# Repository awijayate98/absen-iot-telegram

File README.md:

# absen-iot-telegram

Sistem Absen Menggunaka esp32 + rfid dan di integrasikan dengan database ,dan notifikasi via telegram apabila ada data member baru dan juga ketika tap absen ,dan juga menggunakan tampilan web

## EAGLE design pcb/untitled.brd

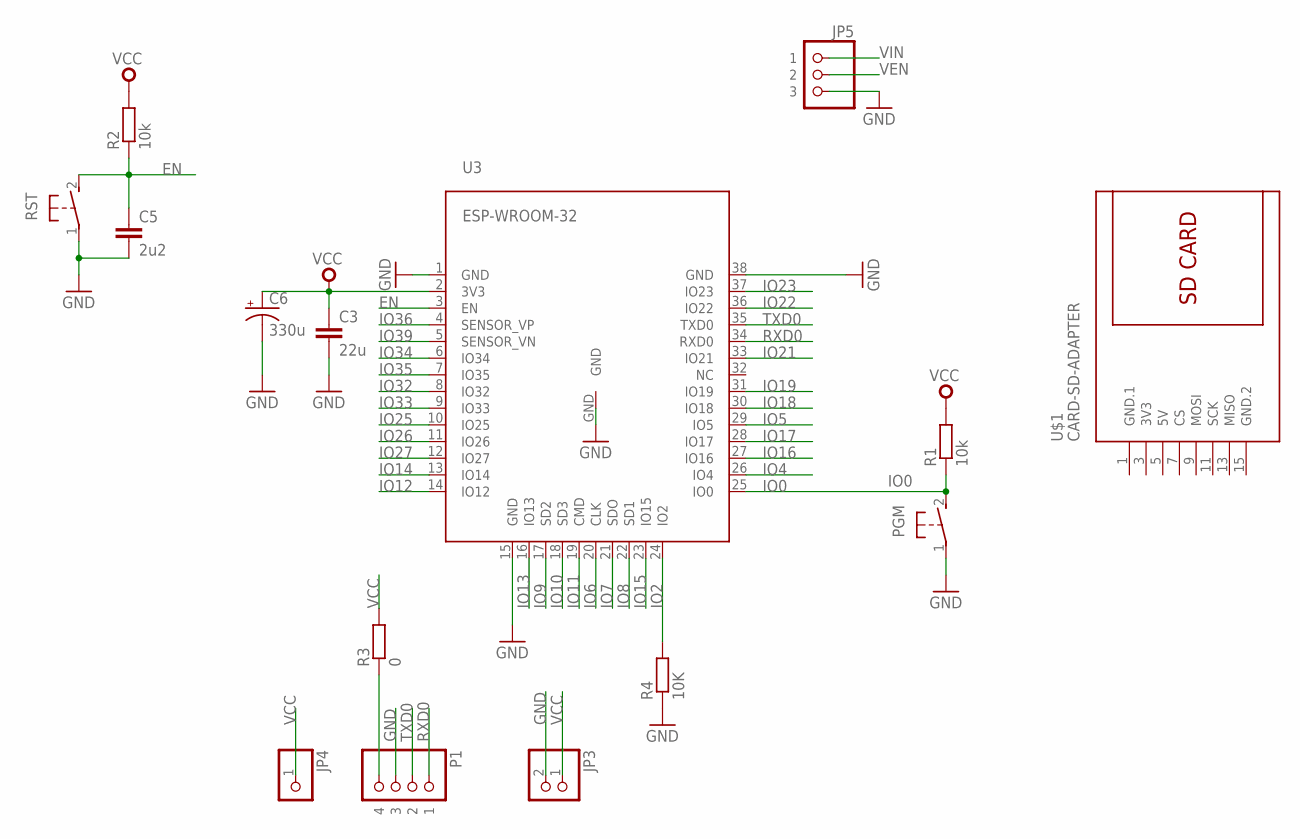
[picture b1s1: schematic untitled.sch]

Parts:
C3: 22u; 0805
C5: 2u2; C0603
C6: 330u; VISHAY_C
JP3: HEADER-1X2ROUND; 1X02_ROUND
JP4: HEADER-1X1ROUND; 1X01_ROUND
JP5: HEADER-1X3ROUND; 1X03_ROUND
P1: HEADER-1X4ROUND; 1X04_ROUND
PGM: DTSM-3
R1, R2: 10k; R0603
R3: 0; R0603
R4: 10K; R0603
RST: DTSM-3
U3: ESP-WROOM-32
U$1: CARD-SD-ADAPTER

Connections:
3V3: U$1.3 (3V3)
5V: U$1.5 (5V)
EN: C5.1, R2.1, RST.2, U3.3 (EN)
GND: C3.2, C5.2, C6.-, JP3.2, JP5.3, P1.3, PGM.1, R4.1, RST.1, U3.1 (GND), U3.15 (GND), U3.38 (GND), U3.GND
GND.1: U$1.1 (GND.1)
GND.2: U$1.15 (GND.2)
IO0: PGM.2, R1.1, U3.25 (IO0)
IO2: R4.2, U3.24 (IO2)
IO4: U3.26 (IO4)
IO5: U3.29 (IO5)
IO6: U3.20 (CLK)
IO7: U3.21 (SDO)
IO8: U3.22 (SD1)
IO9: U3.17 (SD2)
IO10: U3.18 (SD3)
IO11: U3.19 (CMD)
IO12: U3.14 (IO12)
IO13: U3.16 (IO13)
IO14: U3.13 (IO14)
IO15: U3.23 (IO15)
IO16: U3.27 (IO16)
IO17: U3.28 (IO17)
IO18: U3.30 (IO18)
IO19: U3.31 (IO19)
IO21: U3.33 (IO21)
IO22: U3.36 (IO22)
IO23: U3.37 (IO23)
IO25: U3.10 (IO25)
IO26: U3.11 (IO26)
IO27: U3.12 (IO27)
IO32: U3.8 (IO32)
IO33: U3.9 (IO33)
IO34: U3.6 (IO34)
IO35: U3.7 (IO35)
IO36: U3.4 (SENSOR_VP)
IO39: U3.5 (SENSOR_VN)
unnamed: P1.4, R3.1
RXD0: P1.1, U3.34 (RXD0)
TXD0: P1.2, U3.35 (TXD0)
VCC: C3.1, C6.+, JP3.1, JP4.1, R1.2, R2.2, R3.2, U3.2 (3V3)
VEN: JP5.2
VIN: JP5.1

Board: 2 copper layers, 15 parts (10 on the bottom side), 8 nets, no tracks yet.

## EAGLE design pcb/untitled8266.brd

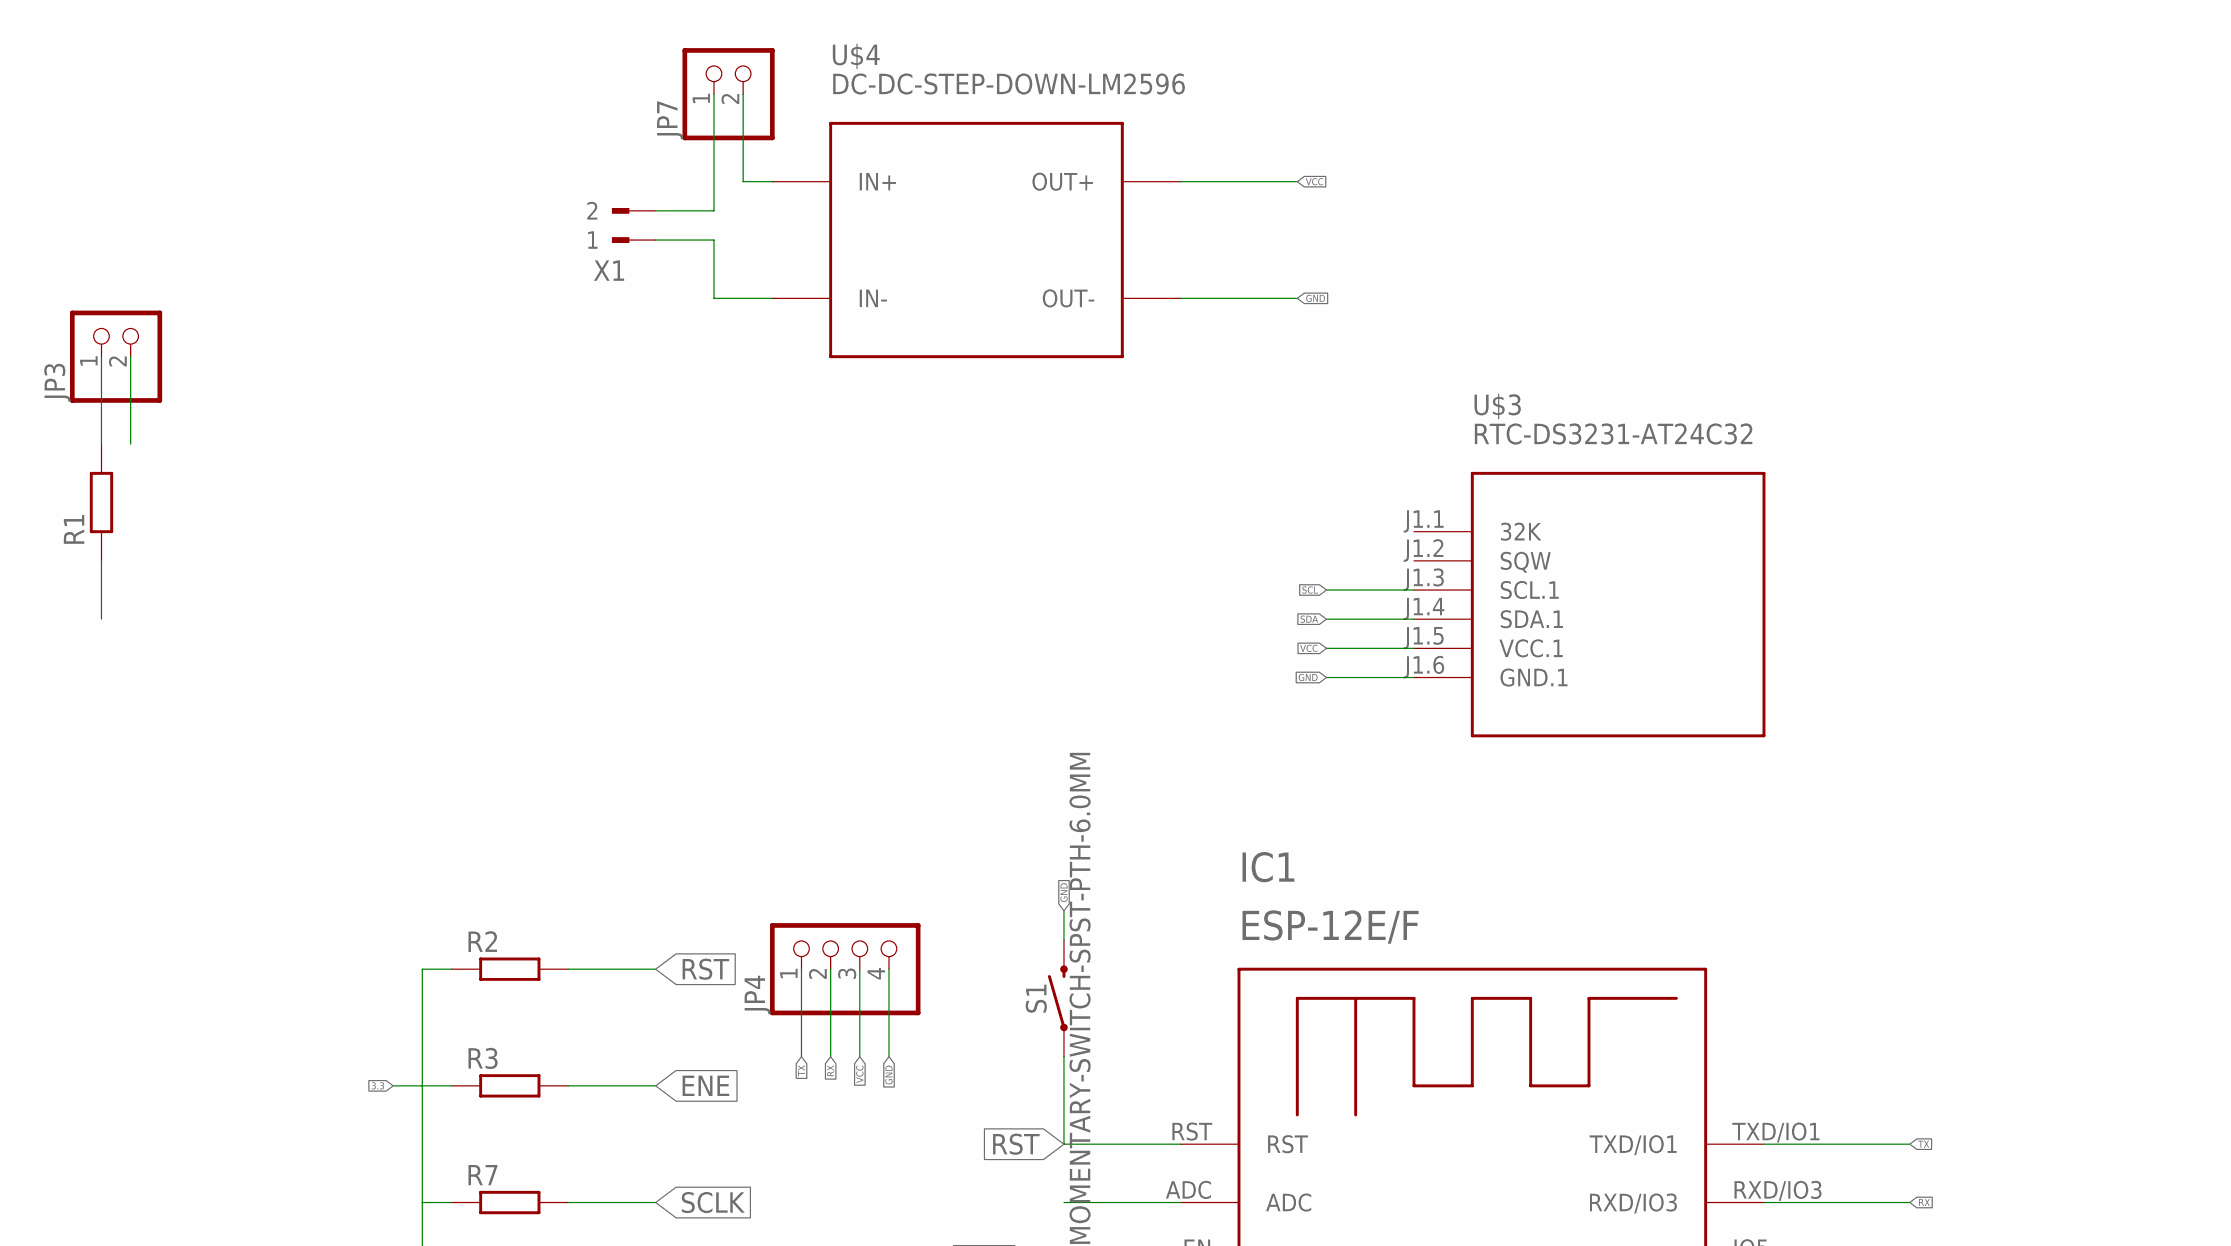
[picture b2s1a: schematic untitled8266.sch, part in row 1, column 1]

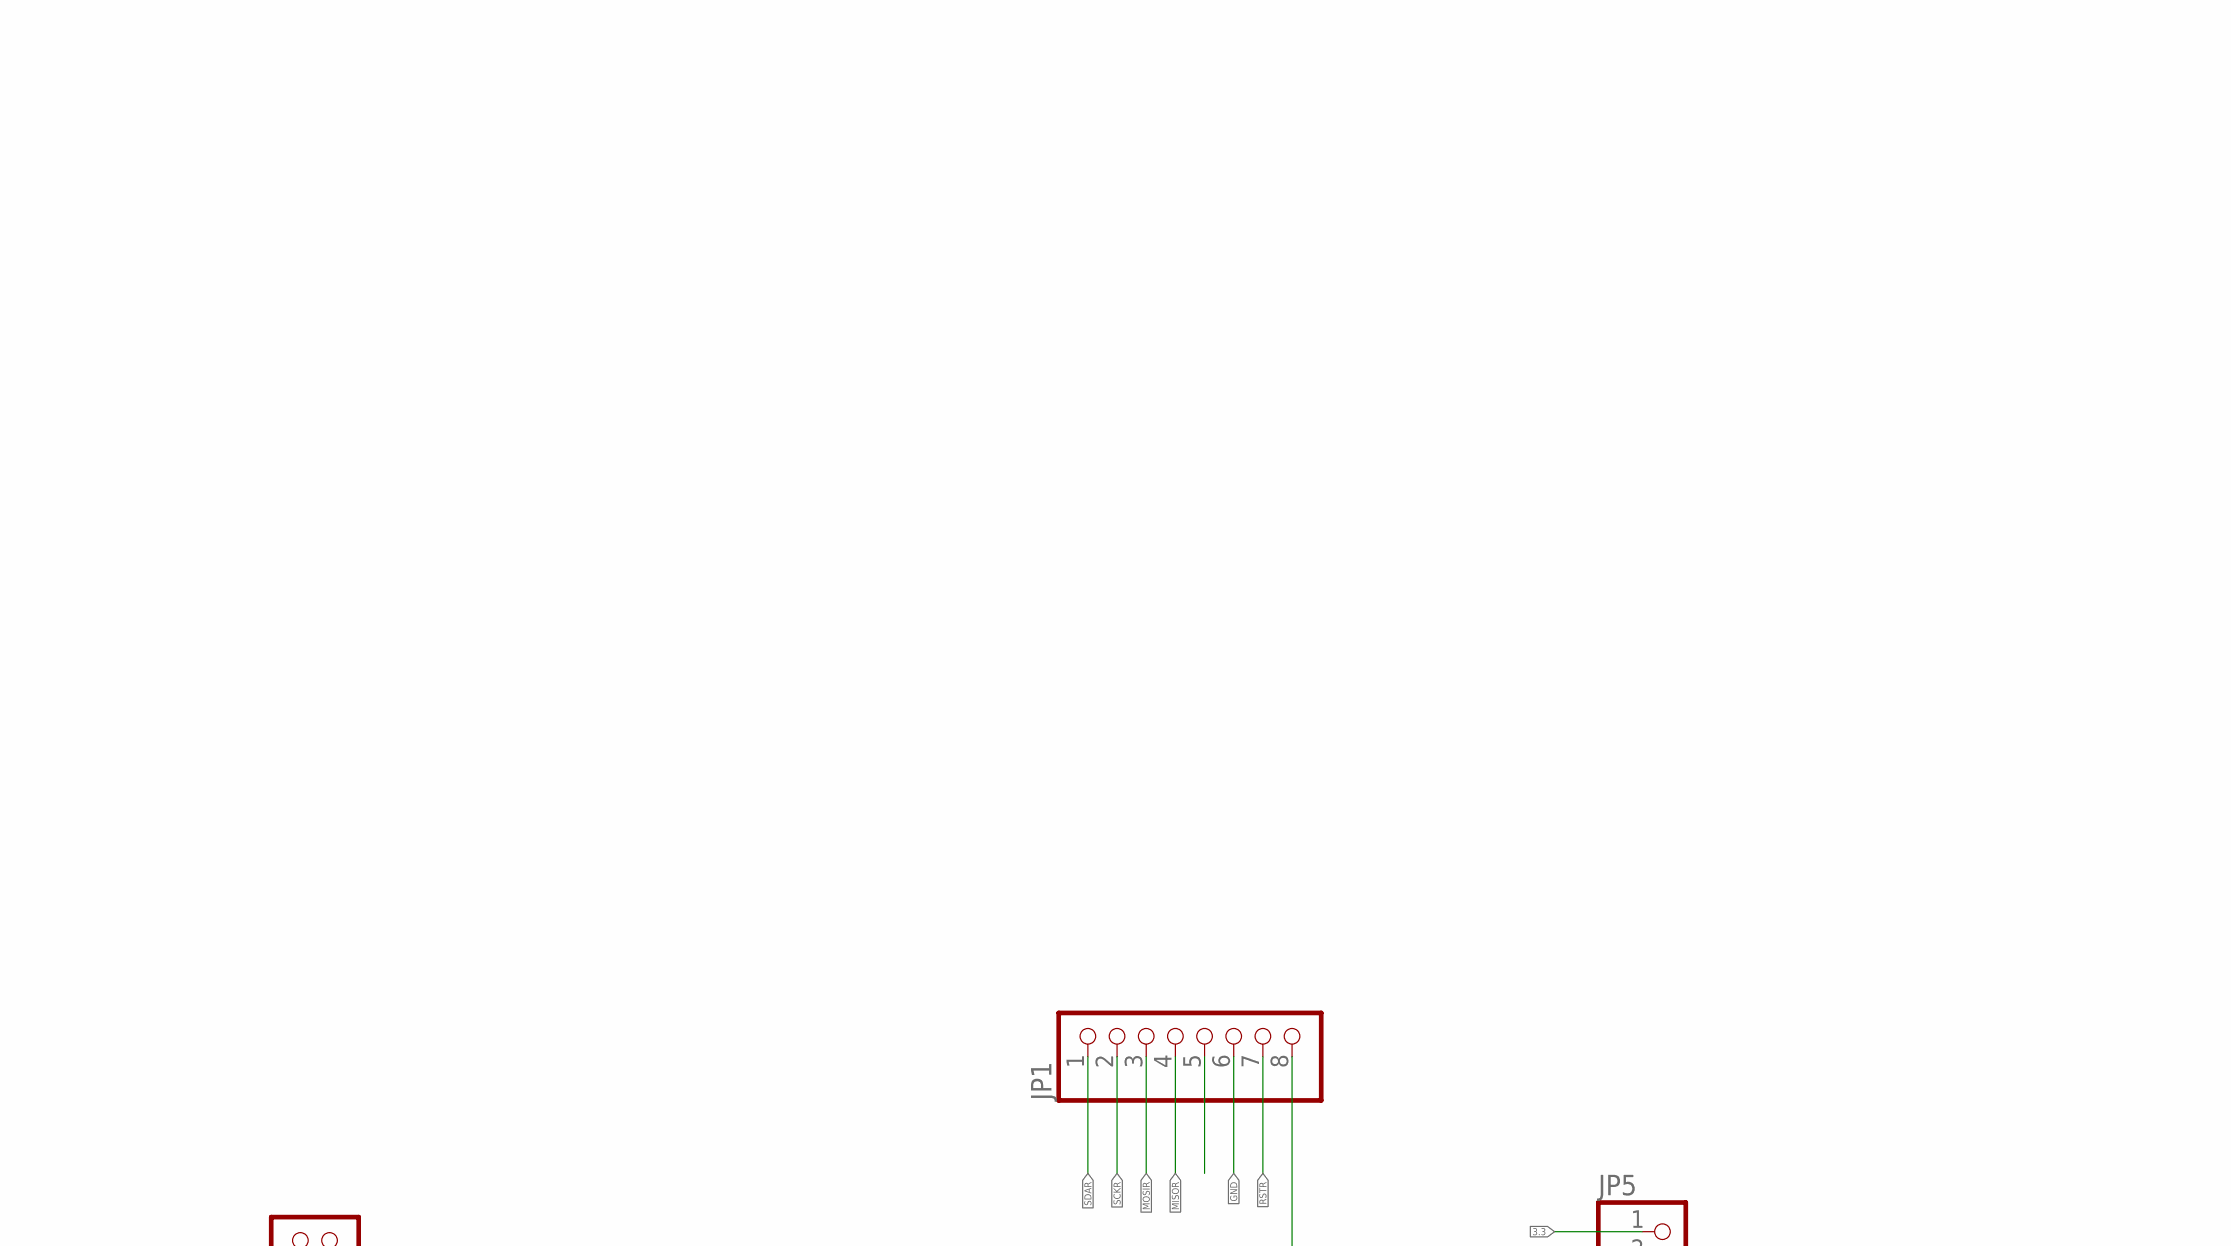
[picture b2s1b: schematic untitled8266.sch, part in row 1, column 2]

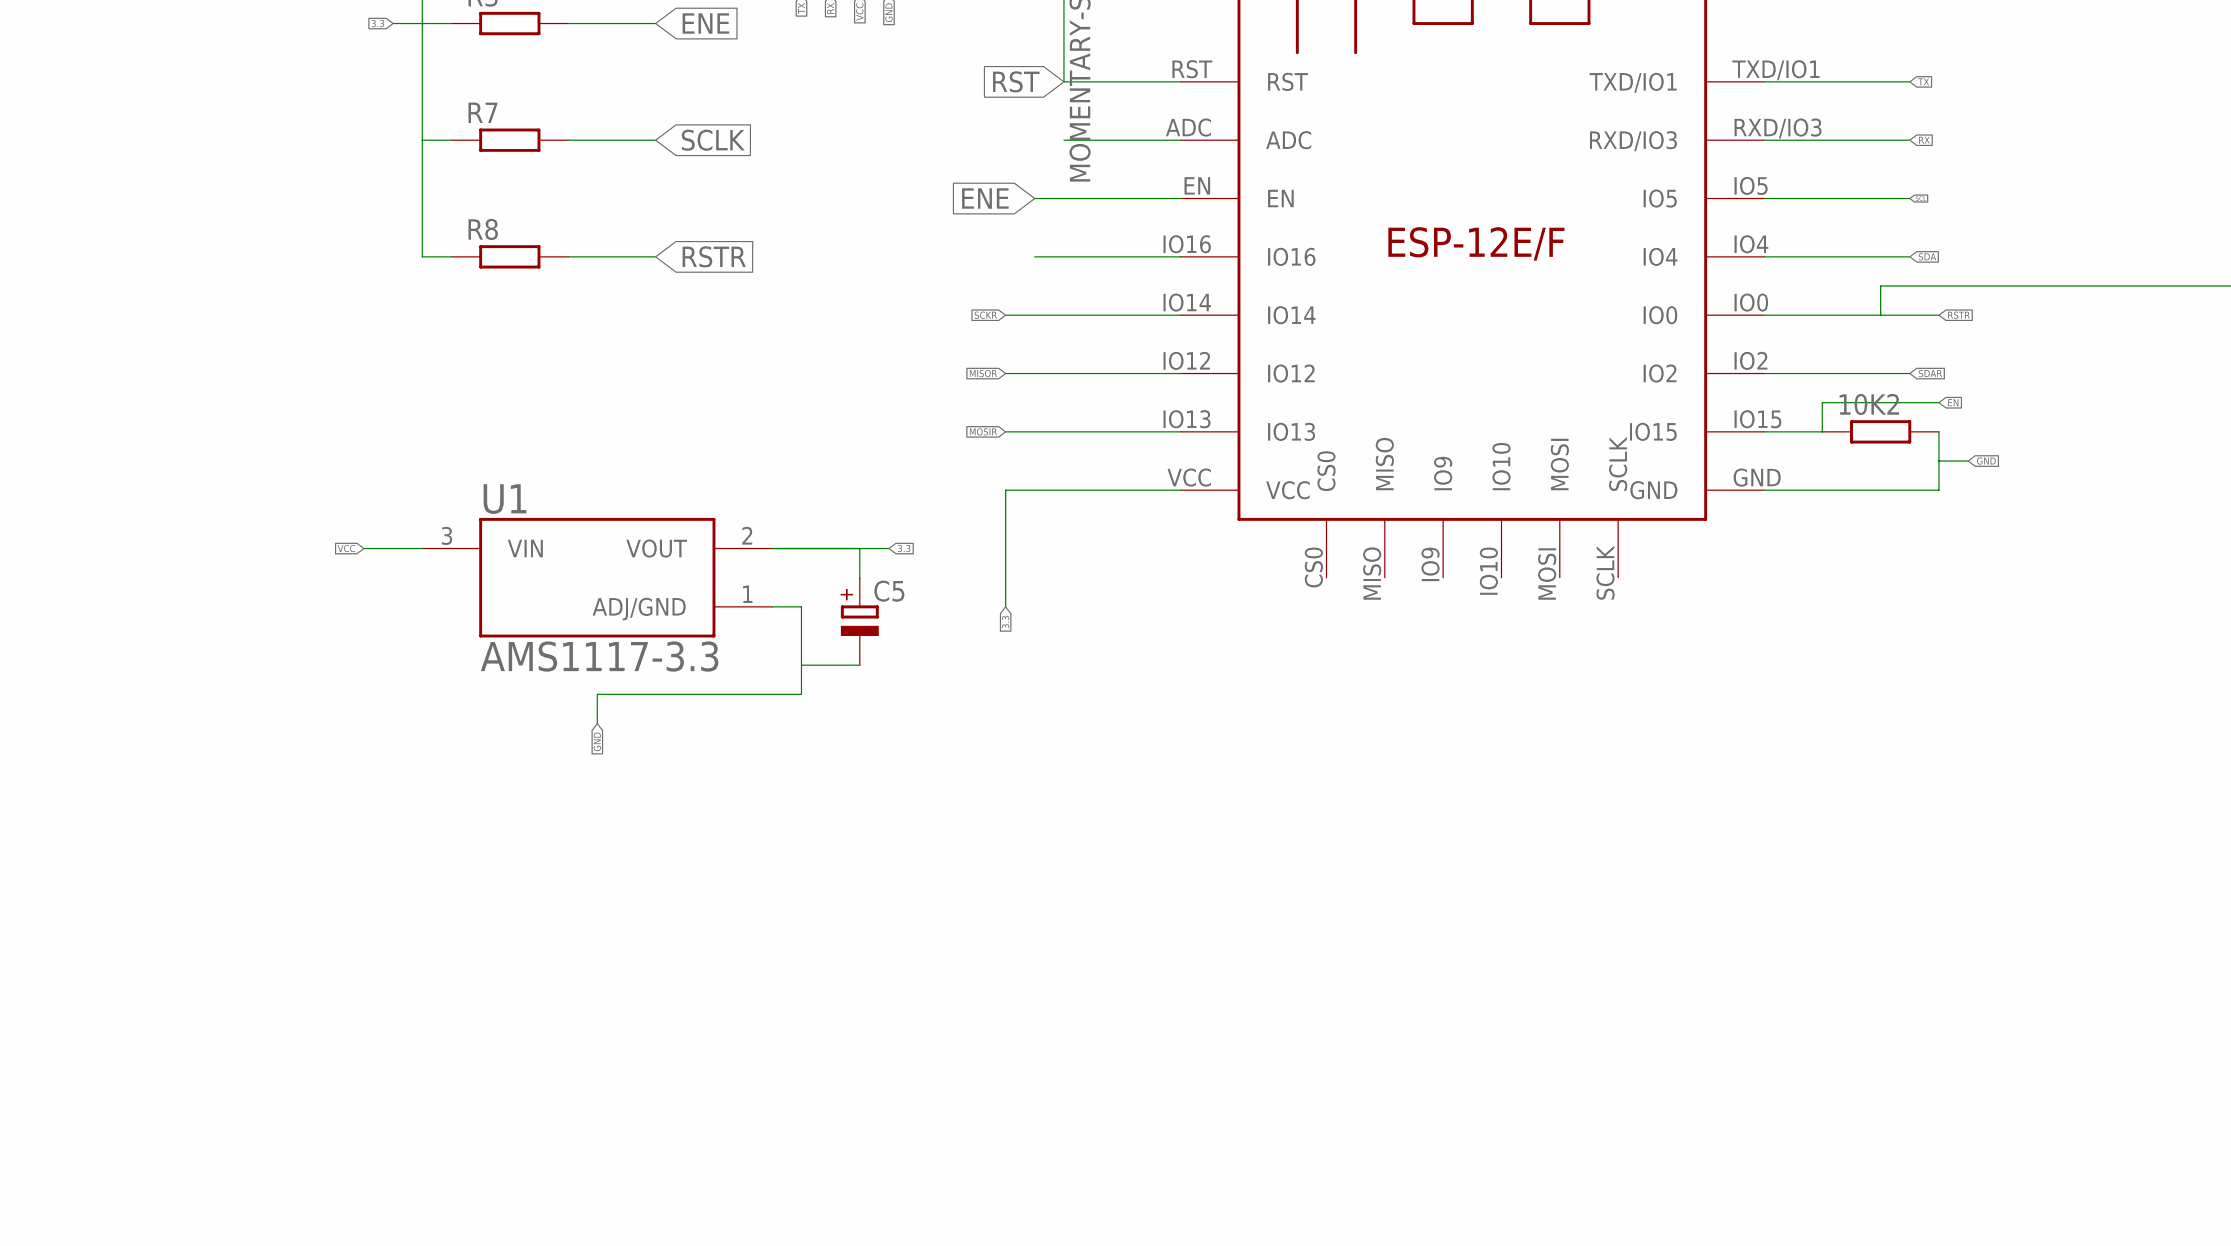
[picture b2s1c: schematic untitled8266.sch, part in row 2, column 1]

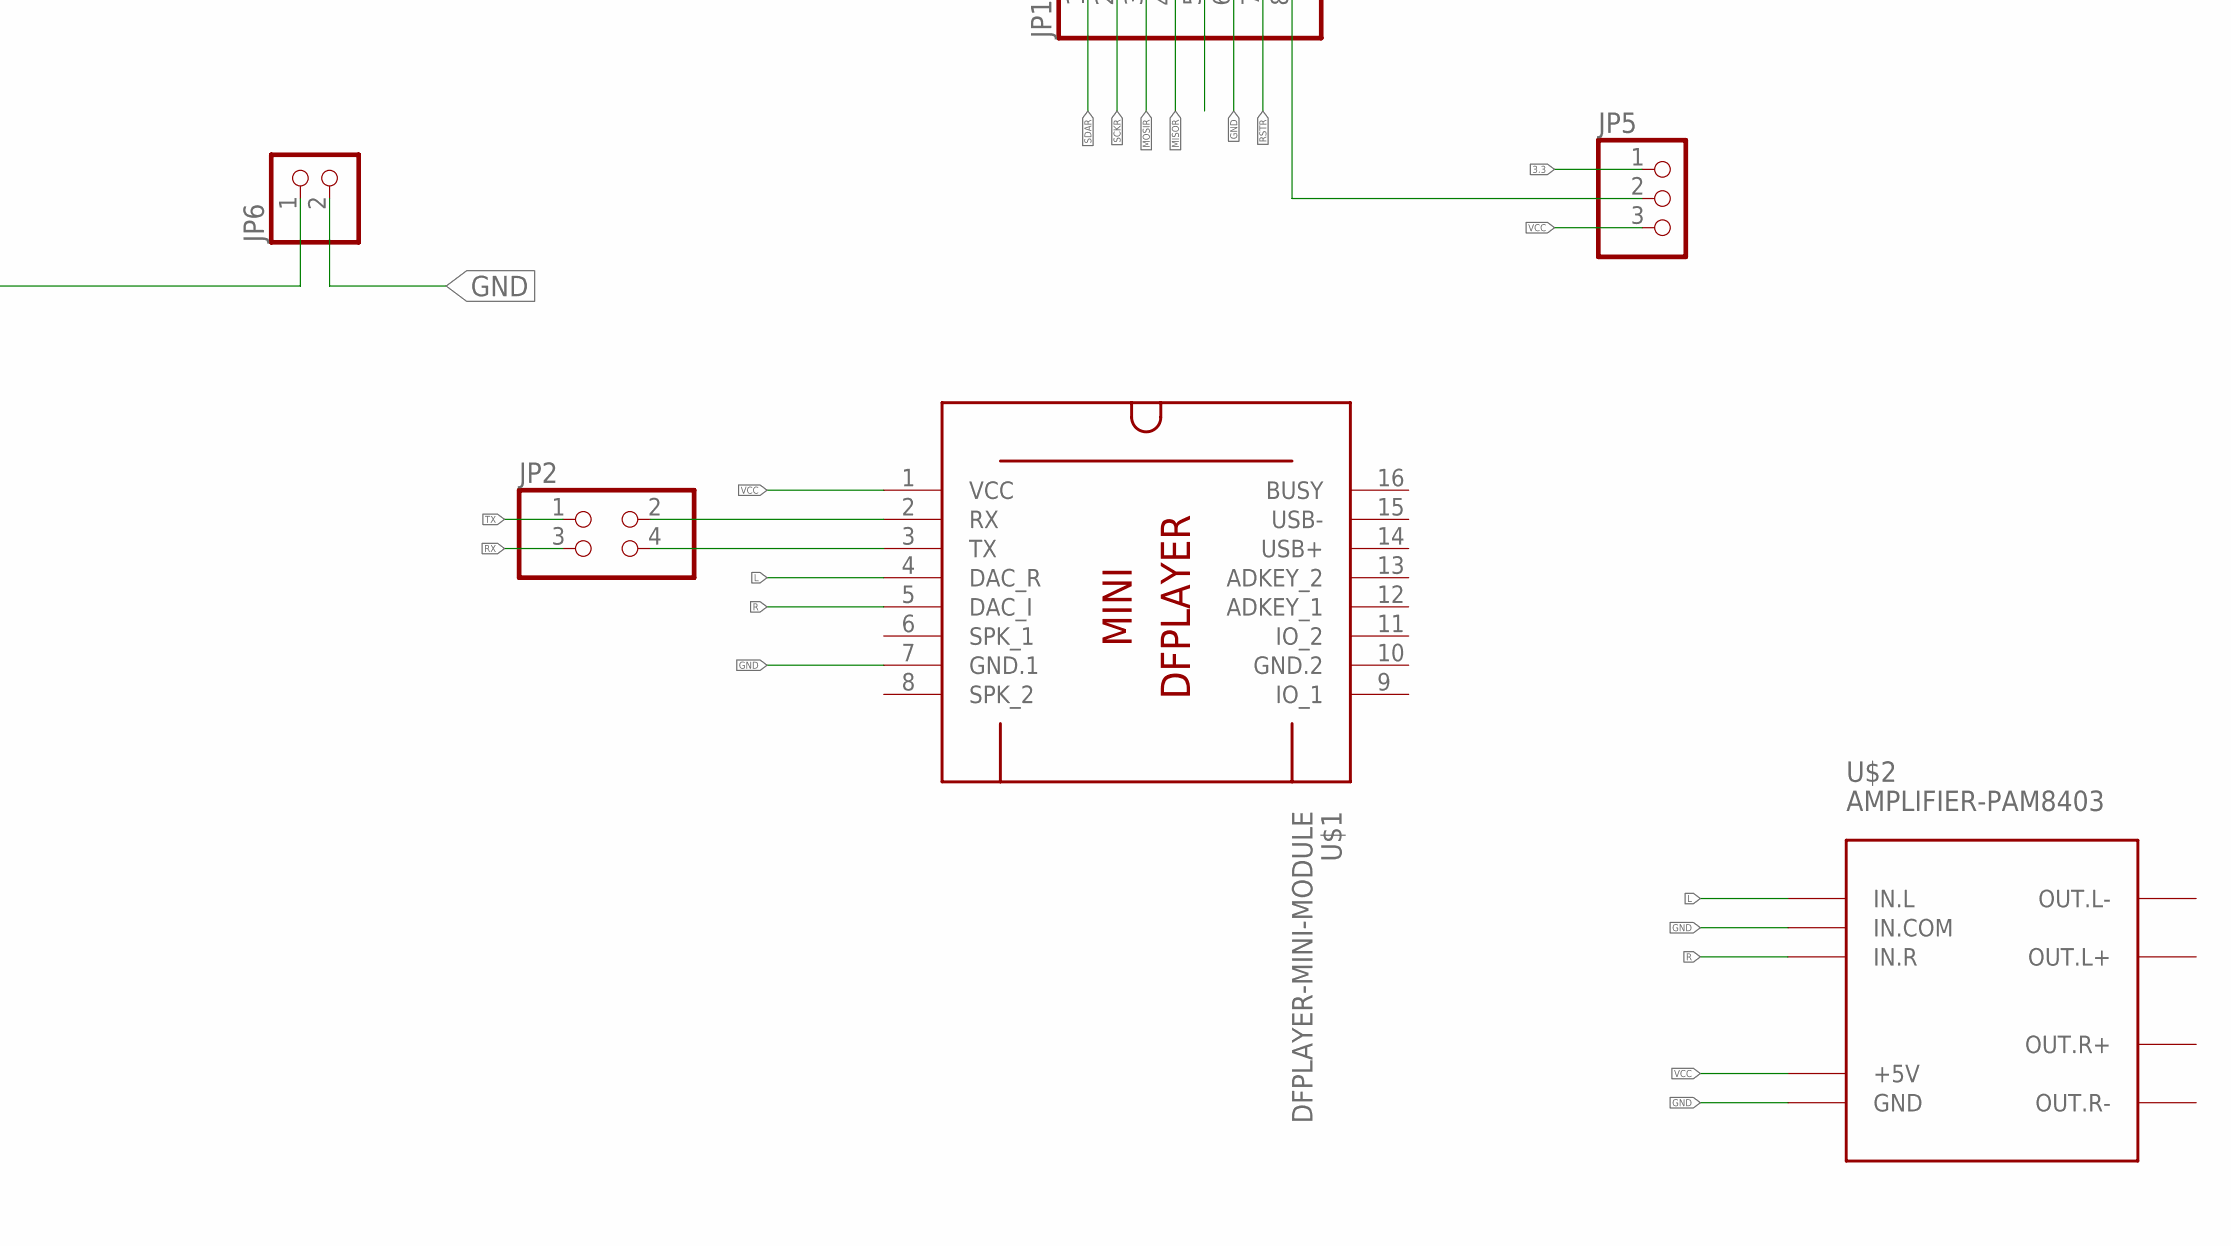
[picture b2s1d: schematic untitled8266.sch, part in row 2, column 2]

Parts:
10K2: R-EU_0207/10; 0207/10
C5: CPOL-EUE5-10.5; E5-10,5
IC1: ESP-12E/F; ESP-12E
JP1: PINHD-1X8; 1X08
JP2: PINHD-2X2; 2X02
JP3, JP6, JP7: PINHD-1X2; 1X02
JP4: PINHD-1X4; 1X04
JP5: PINHD-1X3; 1X03
R1, R2, R3, R7, R8: R-EU_0207/10; 0207/10
S1: MOMENTARY-SWITCH-SPST-PTH-6.0MM; TACTILE_SWITCH_PTH_6.0MM
U1: AMS1117-3.3; SOT229P700X180-4N
U$1: DFPLAYER-MINI-MODULE
U$2: AMPLIFIER-PAM8403
U$3: RTC-DS3231-AT24C32
U$4: DC-DC-STEP-DOWN-LM2596
X1: 180-2

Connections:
3.3: C5.+, IC1.VCC, JP5.1, R2.1, R3.1, R7.1, R8.1, U1.2 (VOUT)
A: JP7.1, X1.2
A0: IC1.ADC
DD: JP2.2, U$1.2 (RX)
DDDD: JP2.4, U$1.3 (TX)
EN: 10K2.1, IC1.IO15
ENE: IC1.EN, R3.2
GND: 10K2.2, C5.-, IC1.GND, JP1.6, JP3.2, JP4.4, JP6.2, S1.3 (2), U1.1 (ADJ/GND), U$1.7 (GND.1), U$2.GND, U$2.IN.COM, U$3.J1.6 (GND.1), U$4.OUT-
GND.2: U$1.10 (GND.2)
L: U$1.4 (DAC_R), U$2.IN.L
MISOR: IC1.IO12, JP1.4
MOSIR: IC1.IO13, JP1.3
unnamed: JP3.1, R1.2
unnamed: JP7.2, U$4.IN+
unnamed: JP1.8, JP5.2
R: U$1.5 (DAC_I), U$2.IN.R
RR: IC1.IO16
RST: IC1.RST, R2.2, S1.1
RSTR: IC1.IO0, JP1.7, JP6.1, R8.2
RX: IC1.RXD/IO3, JP2.3, JP4.2
SCKR: IC1.IO14, JP1.2
SCL: IC1.IO5, U$3.J1.3 (SCL.1)
SCLK: R7.2
SDA: IC1.IO4, U$3.J1.4 (SDA.1)
SDAR: IC1.IO2, JP1.1
TX: IC1.TXD/IO1, JP2.1, JP4.1
V: U$4.IN-, X1.1
VCC: JP4.3, JP5.3, R1.1, U1.3 (VIN), U$1.1 (VCC), U$2.+5V, U$3.J1.5 (VCC.1), U$4.OUT+

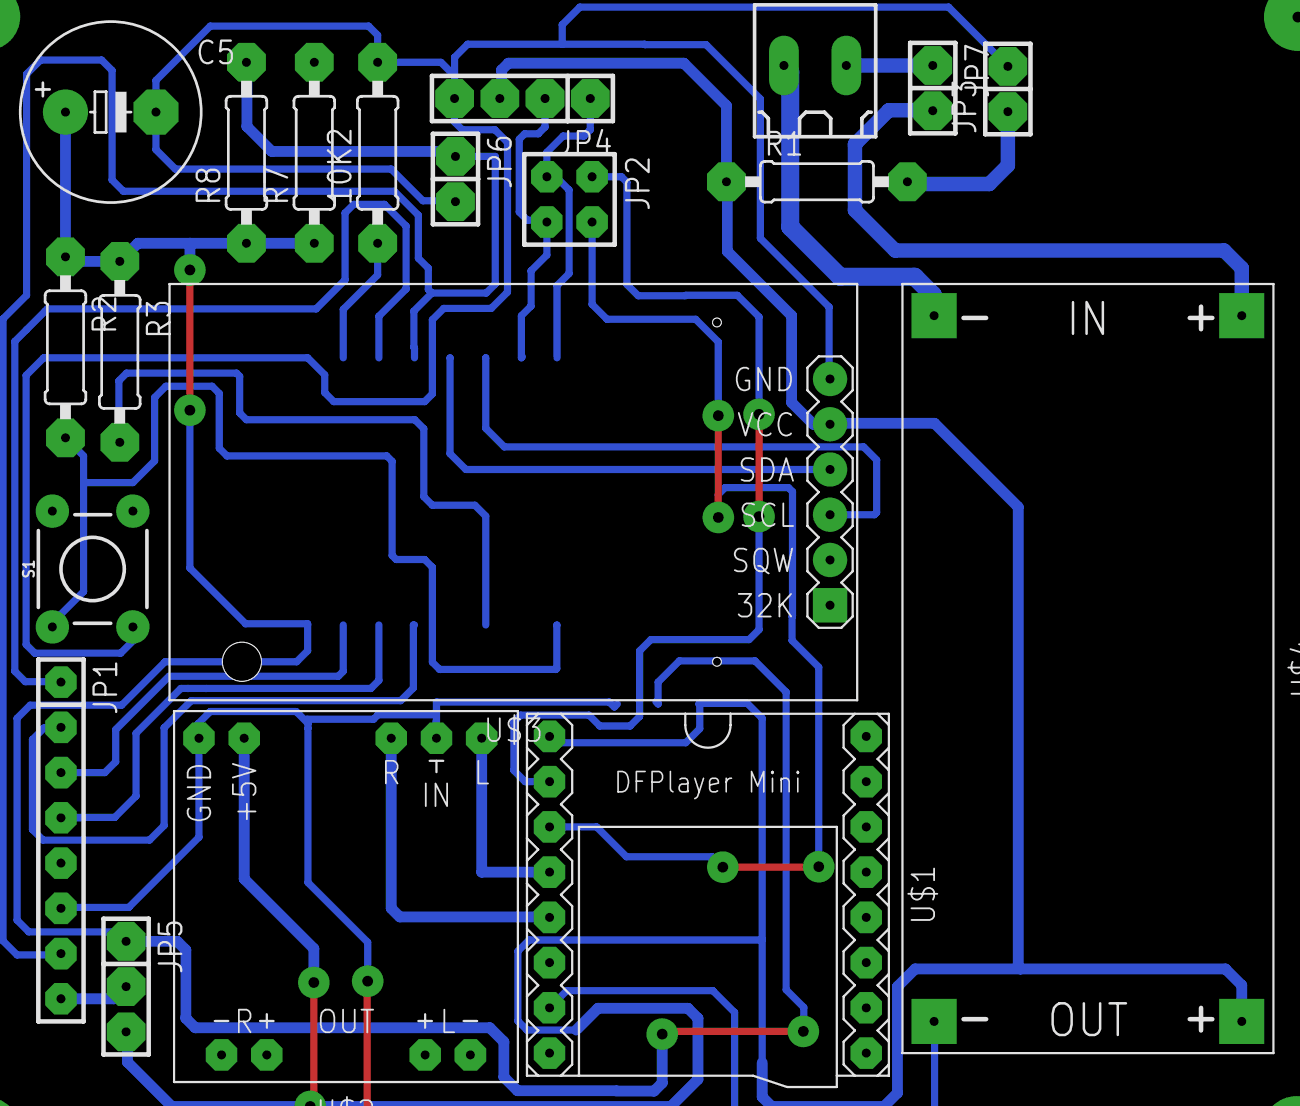
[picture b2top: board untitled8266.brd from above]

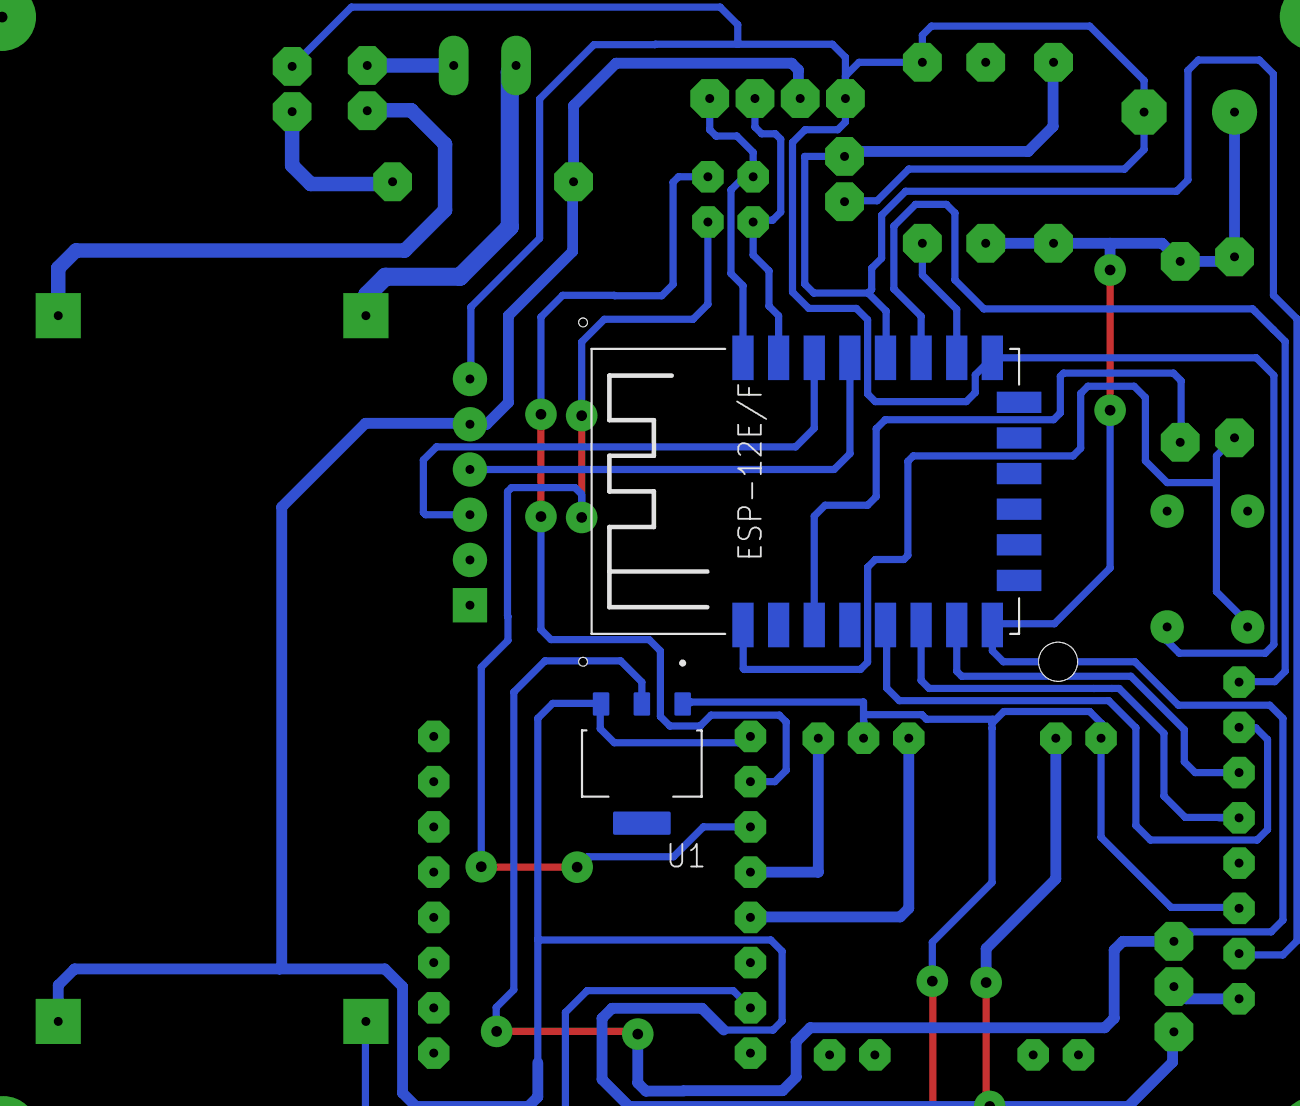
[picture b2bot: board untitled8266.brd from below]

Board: 2 copper layers, 22 parts (2 on the bottom side), 24 nets.

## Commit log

2023-04-26 upload

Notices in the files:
parts and their libraries:
SparkFun-Passives: Licensing: Creative Commons ShareAlike 4.0 International - https://creativecommons.org/licenses/by-sa/4.0
diy-modules: Released under the Creative Commons Attribution 4.0 International License: http://creativecommons.org/licenses/by/4.0
